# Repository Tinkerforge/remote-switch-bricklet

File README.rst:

Remote Switch Bricklet
======================

This repository contains the firmware source code and the hardware design
files. The documentation generator configs can be found at
https://github.com/Tinkerforge/generators

Repository Content
------------------

software/:
 * examples/: Examples for all supported languages
 * build/: Compiled files
 * src/: Source code of firmware
 * Makefile: Makefile to build project

hardware/:
 * Contains KiCad project files and additionally schematics as PDF

datasheets/:
 * Contains datasheets for sensors and complex ICs that are used

Hardware
--------

The hardware is designed with the open source EDA Suite KiCad
(http://www.kicad.org). Before you are able to open the files,
you have to install the Tinkerforge kicad-libraries
(https://github.com/Tinkerforge/kicad-libraries). You can either clone
them directly in hardware/ or clone them in a separate folder and
symlink them into hardware/
(ln -s kicad_path/kicad-libraries project_path/hardware). After that you
can open the .pro file in hardware/ with KiCad and from there view and
modify the schematics and the PCB layout.

Software
--------

If you want to do your own Brick/Bricklet firmware development we highly
recommend that you use our build environment setup script and read the
tutorial (https://www.tinkerforge.com/en/doc/Tutorials/Tutorial_Build_Environment/Tutorial.html).

To compile the C code we recommend you to install the newest GNU Arm Embedded
Toolchain (https://launchpad.net/gcc-arm-embedded/+download).
You also need to install bricklib (https://github.com/Tinkerforge/bricklib)
and brickletlib (https://github.com/Tinkerforge/brickletlib).

You can either clone it directly in software/src/ or clone it in a
separate folder and symlink it into software/src/
(ln -s bricklib_path/bricklib project_path/software/src/ and
ln -s brickletlib_path/brickletlib project_path/software/src/).
Finally make sure to have CMake installed
(http://www.cmake.org/cmake/resources/software.html).

After that you can build the firmware by invoking make in software/.
The firmware (.bin) can then be found in software/build/ and uploaded
with brickv (click button "Flashing" on start screen).

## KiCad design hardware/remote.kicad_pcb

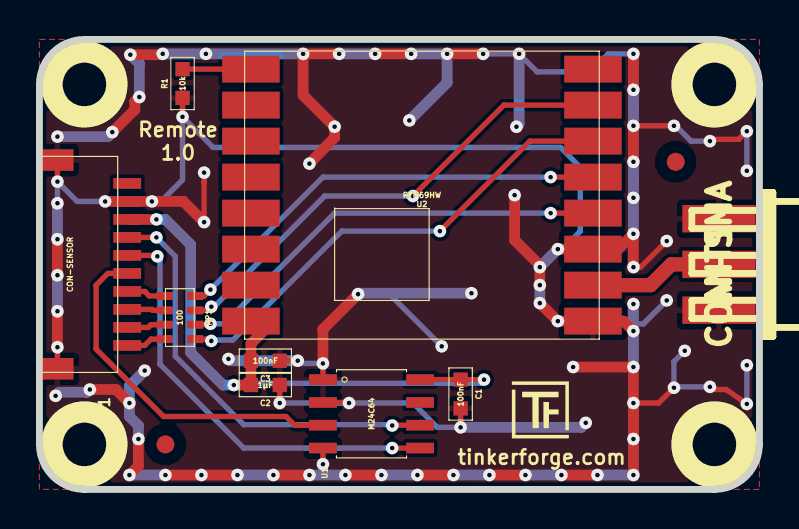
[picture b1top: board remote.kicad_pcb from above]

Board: 2 copper layers, 40.0 x 25.0 mm, 17 parts (0 on the bottom side), 15 nets.

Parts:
ANT1: CON-SMA
C1, C3: 100nF; 0603
C2: 1µF; 0603
Fiducial_Mark: VAL**; Fiducial_Mark
Fiducial_Mark#2: VAL**; Fiducial_Mark
P1: CON-SENSOR
R1: 10k; 0603
RP1: 100; 4X0603
U1: M24C64; SOIC8
U2: RFM69HW
U3, U4, U5, U6: DRILL; DRILL_NP
VAL: CE_5mm
VAL#2: WEEE_7mm

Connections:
GND: ANT1.2, ANT1.3, ANT1.4, ANT1.5, C1.2, C2.1, C3.1, P1.2, P1.EP, R1.1, U1.1, U1.2, U1.4, U2.6, U2.8
unnamed: R1.2, U2.9
unnamed: RP1.2, U2.2
unnamed: P1.8, RP1.7
unnamed: P1.9, RP1.6
unnamed: P1.10, RP1.5
unnamed: RP1.1, U2.4
unnamed: RP1.4, U2.3
unnamed: RP1.3, U2.5
unnamed: ANT1.1, U2.7
unnamed: P1.7, RP1.8
unnamed: P1.6, U1.3
unnamed: P1.5, U1.5
unnamed: P1.4, U1.6
VCC: C1.1, C2.2, C3.2, P1.3, U1.8, U2.16

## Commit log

2013-07-29 Initial commit of Remote Switch Bricklet firmware
2013-08-21 windows: Don't trigger a build in generate_makefile.bat
    Also use normal make instead of a special named one.
2013-08-21 Change name from "tries" to "repeats"
2013-09-17 Add examples for Remote Switch Bricklet
2013-10-15 add hardware files
2013-12-09 Fix hose code in examples
    Document house and receiver code example better
2013-12-15 Fix bit order in examples
2013-12-18 Add socket type a/b API
2013-12-19 Add new adressing type C
2013-12-19 examples: Fix bitorder of receiver code
2013-12-19 Udpate changelog
2014-01-10 Add Perl examples
2014-01-15 php: Use const for constant values
2014-02-07 Add Mathematica examples
2014-02-10 perl: fixed namespace
2014-02-12 javascript: add examples
2014-02-18 javascript: examples fixed
2014-02-20 javascript: fixed example
2014-02-20 javascript: add html examples
2014-02-24 javascript: port 4280, startExample()
2014-02-28 javascript: Break long lines and cleanup whitespace
2014-03-05 Add LabVIEW example
2014-03-06 labview: Add example in LV2010 format
2014-03-27 matlab: add examples
2014-04-02 java: Unify constants style
2014-04-02 perl: Unify print style
2014-04-17 matlab: Remove \n prefix from input line
2014-04-17 matlab: Add parentheses to make pygments happy
2014-07-15 java: Replace System.console() usage with an Eclipse compatible pattern
2014-07-29 Fix typos and improve wording in all examples, sync Perl example
2014-12-03 update silkscreen outlines
2014-12-15 updated versions with thin silkscreen lines
2015-02-13 csharp,vbnet: Use ReadLine instead of ReadKey
    Because ReadKey doesn't work with a pipe as stdin on the RED Brick.
2015-03-02 windows: Stop cmake from searching for mingw32-make.exe
    Using MinGW Makefiles as generator makes cmake search for mingw32-make.exe
    which might not be installed because GnuWin32's make.exe is used instead.
2015-04-09 c: Whitespace
2015-07-25 Make JavaScript browser example textarea readonly
2015-07-27 Cleanup C/C++, C#, Java, Python and Ruby examples
2015-07-29 Reformat changelog
2015-08-07 Use full device class name in Python example
2015-08-12 Fix minor warnings in C/C++ example
2015-08-14 Add missing comment in Delphi examples
2015-08-19 Cleanup Perl example
2015-09-09 Duplicate cmake call to fix bug during cmake creation
2015-09-24 Generator based example cleanup
2015-11-12 matlab: Fix callback handling for R2014a
    http://undocumentedmatlab.com/blog/matlab-callbacks-for-java-events-in-r2014a
2015-11-25 Include date and commit into changelog
2016-05-18 c: Add missing device destroy call
2016-07-01 Make the change UID comment more explicit
2017-03-06 labview: Fix wrong connection in example
2017-04-20 shell: Adapt example
2017-06-02 octave: Use javaObject instead of deprecated java_new
2017-12-07 mathematica: Also generate .nb files
2018-02-19 javascript: Close div tag correctly
2018-02-20 Cleanup KiCad libraries config
    Ensure LibDir=kicad-libraries and LibName1=tinkerforge.
    Remove special library.
2018-05-11 Rename files
2018-05-24 perl: Use strict in examples
2018-05-28 mathematica: Fix namespace
2018-07-11 Add Makefile with docker support
2018-07-11 Update directory structure and build instructions
2018-07-11 Remove obsolete generate_makefile scripts
2018-11-06 Add rust examples
2018-11-07 rust: Accept host names for ip connection, fix naming inconsistencies
2018-12-14 Add go examples.
2018-12-18 go: Change import path.
2018-12-18 go: Change import path again.
2018-12-20 rust: Reformat examples.
2019-01-24 mqtt: Add examples.
2019-01-24 mqtt: Fix example header.
2019-01-24 mqtt: Remove executable bit in example permissions.
2019-01-24 go: Minor example fixes.
2020-01-13 examples: Use python3 input instead of python2 raw_input.
2020-03-16 Whitespace
2020-04-07 examples: rust: Always block when calling bindings functions.
2021-10-25 Update KiCad link
    https://www.kicad.org/blog/2021/10/Avoid-links-to-former-kicad-domain/
2022-07-06 Add license files.

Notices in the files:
hardware/remote.kicad_pcb:
Licensed under CERN OHL v.1.1
Copyright (©) 2013, B.Nordmeyer
Copyright Tinkerforge GmbH 2013.
This documentation describes Open Hardware and is licensed under the
CERN OHL v. 1.1.
